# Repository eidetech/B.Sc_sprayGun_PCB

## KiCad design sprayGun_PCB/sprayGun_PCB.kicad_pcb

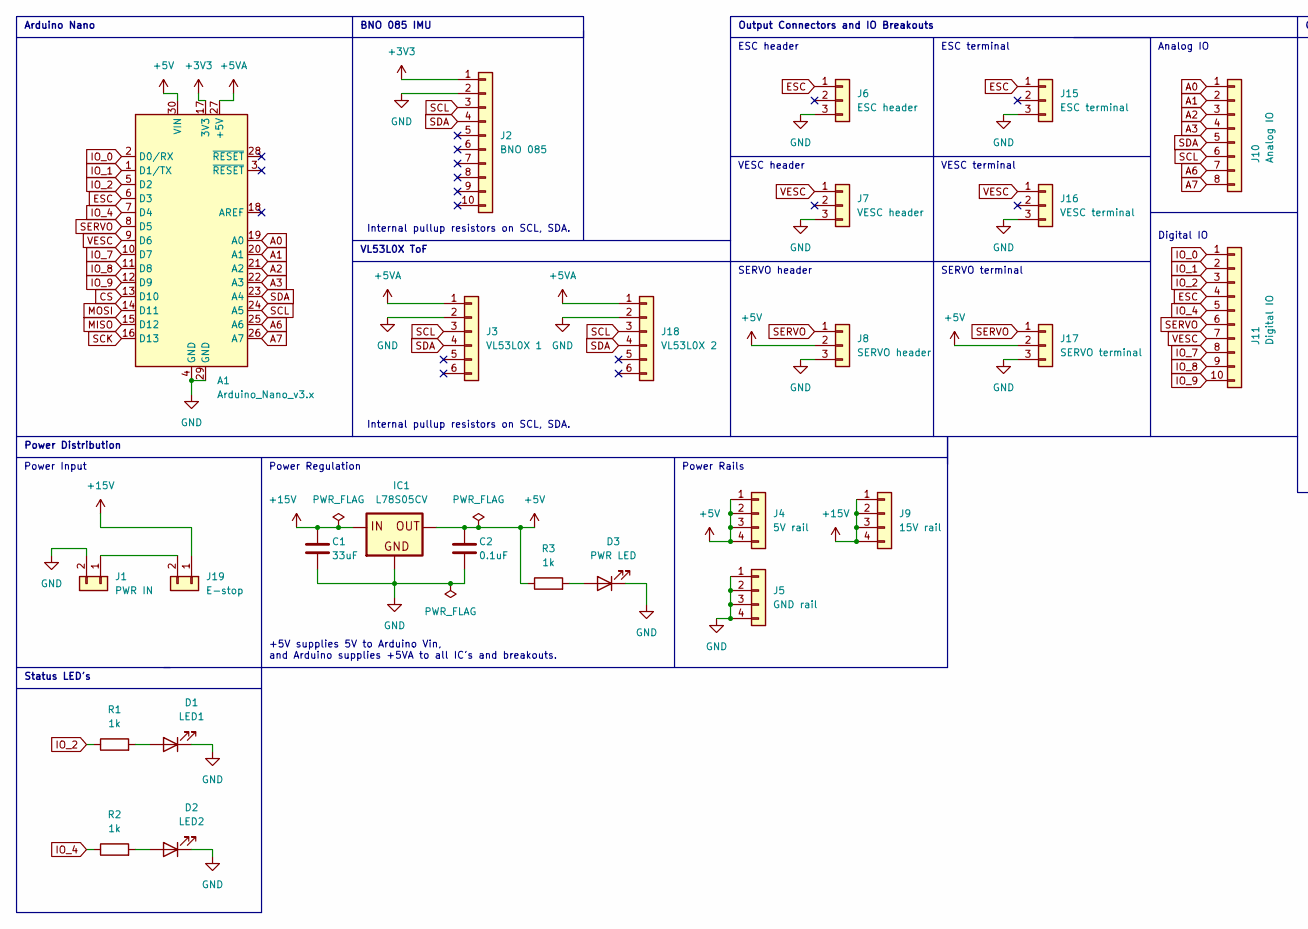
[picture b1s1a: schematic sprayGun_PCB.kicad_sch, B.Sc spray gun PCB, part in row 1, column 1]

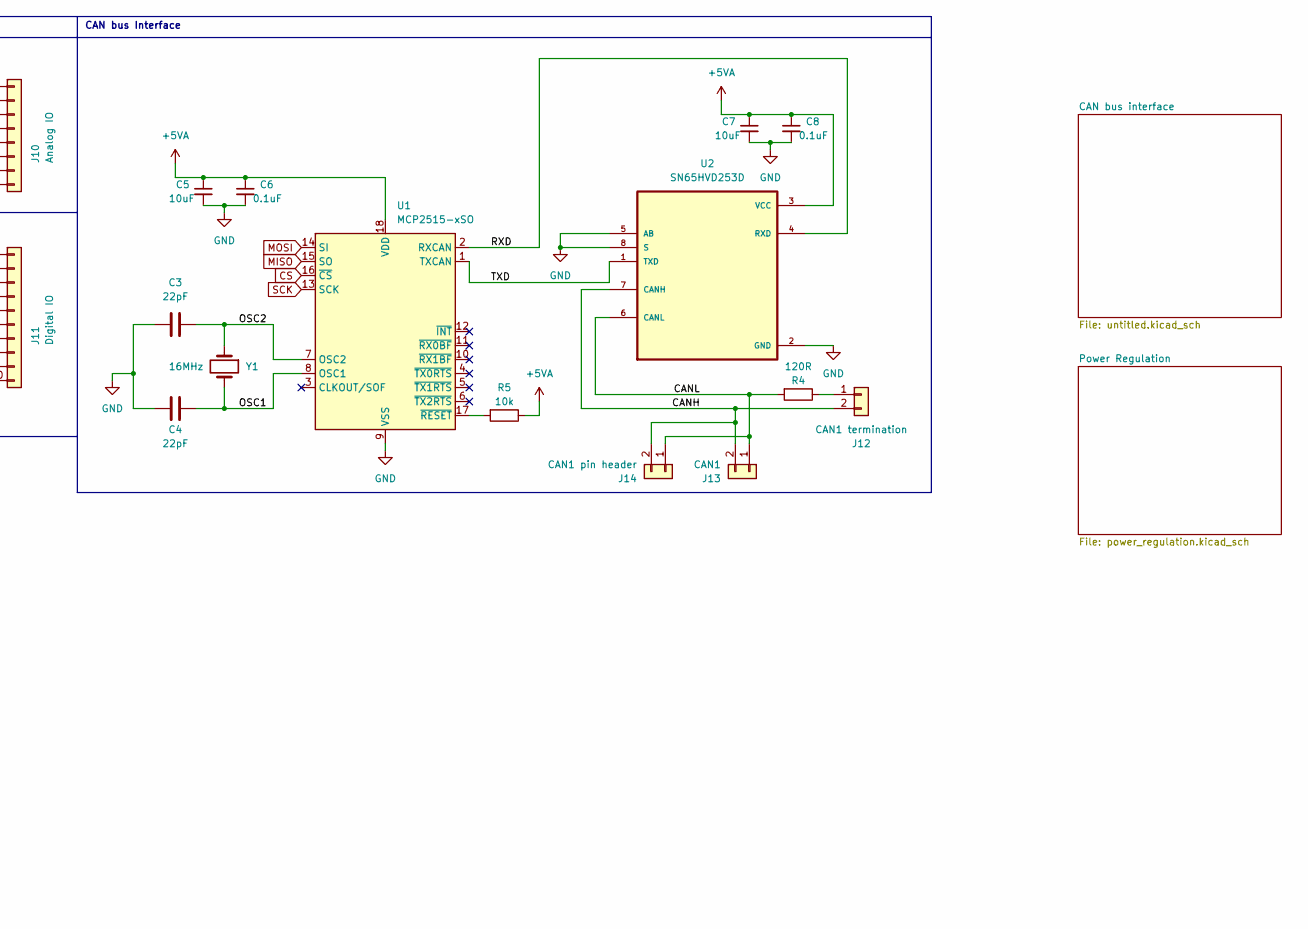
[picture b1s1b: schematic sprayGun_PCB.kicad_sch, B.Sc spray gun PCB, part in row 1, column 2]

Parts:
A1: Arduino_Nano_v3.x; Arduino_Nano
C1: 33uF; CP_Radial_D6.3mm_P2.50mm
C2, C6, C8: 0.1uF; CP_Radial_D5.0mm_P2.50mm
C3, C4: 22pF; CP_Radial_Tantal_D5.0mm_P2.50mm
C5, C7: 10uF; CP_Radial_D5.0mm_P2.00mm
D1: LED1; LED_D5.0mm
D2: LED2; LED_D5.0mm
D3: PWR LED; LED_D5.0mm
IC1: L78S05CV
J1: PWR IN; TerminalBlock_Phoenix_MKDS-3-2-5.08_1x02_P5.08mm_Horizontal
J2: BNO 085; PinSocket_1x10_P2.54mm_Vertical
J3: VL53L0X 1; JST_XH_B6B-XH-A_1x06_P2.50mm_Vertical
J4: 5V rail; TerminalBlock_Phoenix_MKDS-3-4-5.08_1x04_P5.08mm_Horizontal
J5: GND rail; TerminalBlock_Phoenix_MKDS-3-4-5.08_1x04_P5.08mm_Horizontal
J6: ESC header; PinHeader_1x03_P2.54mm_Vertical
J7: VESC header; PinHeader_1x03_P2.54mm_Vertical
J8: SERVO header; PinHeader_1x03_P2.54mm_Vertical
J9: 15V rail; TerminalBlock_Phoenix_MKDS-3-4-5.08_1x04_P5.08mm_Horizontal
J10: Analog IO; TerminalBlock_Phoenix_MKDS-3-8-5.08_1x08_P5.08mm_Horizontal
J11: Digital IO; TerminalBlock_Phoenix_MKDS-3-10-5.08_1x10_P5.08mm_Horizontal
J12: CAN1 termination; PinHeader_1x02_P2.54mm_Vertical
J13: CAN1; TerminalBlock_Phoenix_MKDS-3-2-5.08_1x02_P5.08mm_Horizontal
J14: CAN1 pin header; PinHeader_1x02_P2.54mm_Vertical
J15: ESC terminal; TerminalBlock_Phoenix_MKDS-3-3-5.08_1x03_P5.08mm_Horizontal
J16: VESC terminal; TerminalBlock_Phoenix_MKDS-3-3-5.08_1x03_P5.08mm_Horizontal
J17: SERVO terminal; TerminalBlock_Phoenix_MKDS-3-3-5.08_1x03_P5.08mm_Horizontal
J18: VL53L0X 2; JST_XH_B6B-XH-A_1x06_P2.50mm_Vertical
J19: E-stop; TerminalBlock_Phoenix_MKDS-3-2-5.08_1x02_P5.08mm_Horizontal
R1, R2, R3: 1k; R_Axial_DIN0207_L6.3mm_D2.5mm_P10.16mm_Horizontal
R4: 120R; R_Axial_DIN0207_L6.3mm_D2.5mm_P10.16mm_Horizontal
R5: 10k; R_Axial_DIN0207_L6.3mm_D2.5mm_P10.16mm_Horizontal
U1: MCP2515-xSO; SOIC-18W_7.5x11.6mm_P1.27mm
U2: SN65HVD253D
Y1: 16MHz; Crystal_HC49-4H_Vertical

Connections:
+3V3: A1.17 (3V3), J2.1
+5V: A1.30 (VIN), C2.1, IC1.3, J4.1, J4.2, J4.3, J4.4, J8.2, J17.2, R3.1
+5VA: A1.27 (+5V), C5.1, C6.1, C7.1, C8.1, J3.1, J18.1, R5.1, U1.18 (VDD), U2.3 (VCC)
+15V: C1.1, IC1.1, J9.1, J9.2, J9.3, J9.4, J19.1
/CANH: J12.2, J13.2, J14.2, U2.7 (CANH)
/CANL: J13.1, J14.1, R4.2, U2.6 (CANL)
/OSC1: C4.2, U1.8 (OSC1), Y1.2
/OSC2: C3.2, U1.7 (OSC2), Y1.1
/RXD: U1.2 (RXCAN), U2.4 (RXD)
/TXD: U1.1 (TXCAN), U2.1 (TXD)
A0: A1.19 (A0), J10.1
A1: A1.20 (A1), J10.2
A2: A1.21 (A2), J10.3
A3: A1.22 (A3), J10.4
A6: A1.25 (A6), J10.7
A7: A1.26 (A7), J10.8
CS: A1.13 (D10), U1.16 (~CS)
ESC: A1.6 (D3), J6.1, J11.4, J15.1
GND: A1.4 (GND), A1.29 (GND), C1.2, C2.2, C3.1, C4.1, C5.2, C6.2, C7.2, C8.2, D1.1 (K), D2.1 (K), D3.1 (K), IC1.2, J1.2, J2.2, J3.2, J5.1, J5.2, J5.3, J5.4, J6.3, J7.3, J8.3, J15.3, J16.3, J17.3, J18.2, U1.9 (VSS), U2.2 (GND), U2.5 (AB), U2.8 (S)
IO_0: A1.2 (D0/RX), J11.1
IO_1: A1.1 (D1/TX), J11.2
IO_2: A1.5 (D2), J11.3, R1.1
IO_4: A1.7 (D4), J11.5, R2.1
IO_7: A1.10 (D7), J11.8
IO_8: A1.11 (D8), J11.9
IO_9: A1.12 (D9), J11.10
MISO: A1.15 (D12), U1.15 (SO)
MOSI: A1.14 (D11), U1.14 (SI)
unnamed: D1.2 (A), R1.2
unnamed: D2.2 (A), R2.2
unnamed: D3.2 (A), R3.2
unnamed: J1.1, J19.2
unnamed: J12.1, R4.1
unnamed: R5.2, U1.17 (~RESET)
SCK: A1.16 (D13), U1.13 (SCK)
SCL: A1.24 (A5), J2.3, J3.3, J10.6, J18.3
SDA: A1.23 (A4), J2.4, J3.4, J10.5, J18.4
SERVO: A1.8 (D5), J8.1, J11.6, J17.1
VESC: A1.9 (D6), J7.1, J11.7, J16.1

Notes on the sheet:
Internal pullup resistors on SCL, SDA.
Power Rails
SERVO terminal
Digital IO
Analog IO
ESC terminal
+5V supplies 5V to Arduino Vin, and Arduino supplies +5VA to all IC's and breakouts.
VESC header
ESC header
Power Input
Output Connectors and IO Breakouts
BNO 085 IMU
Arduino Nano
CAN bus Interface
Power Regulation
Power Distribution
VL53L0X ToF
VESC terminal
SERVO header
Status LED's

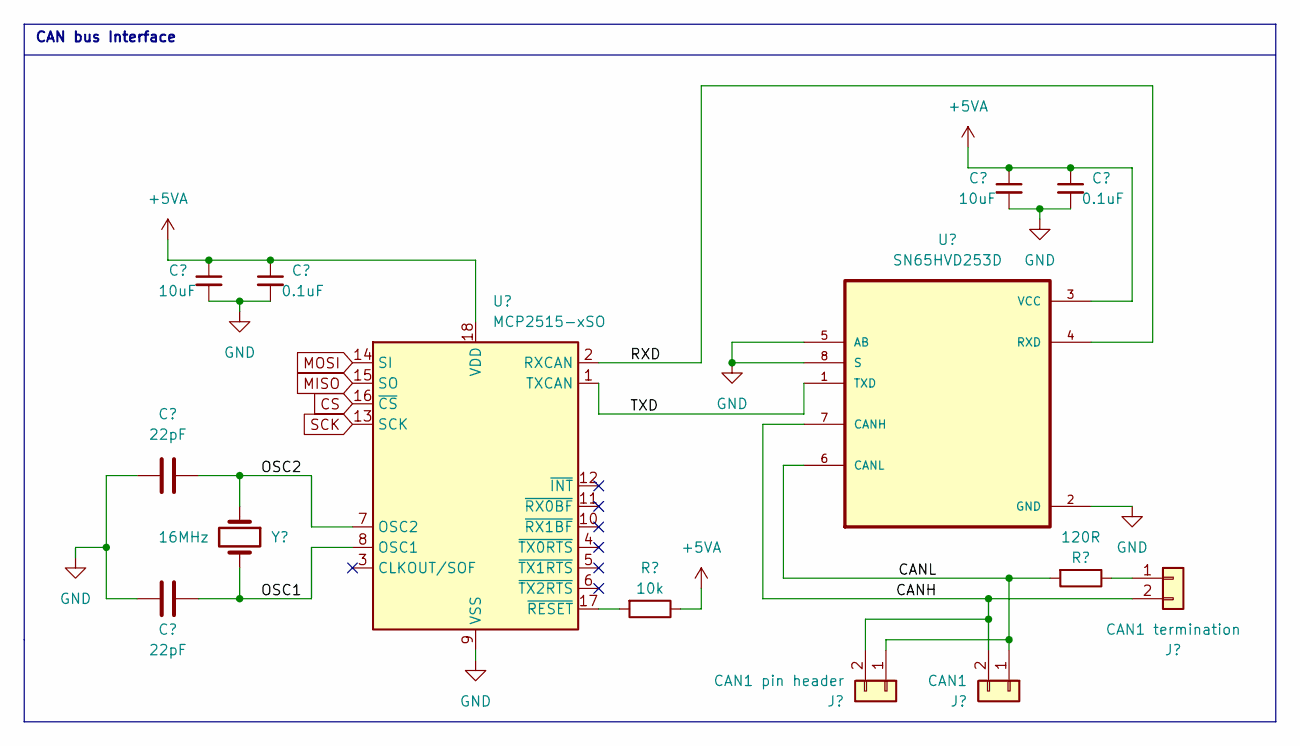
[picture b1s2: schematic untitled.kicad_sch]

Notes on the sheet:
CAN bus Interface

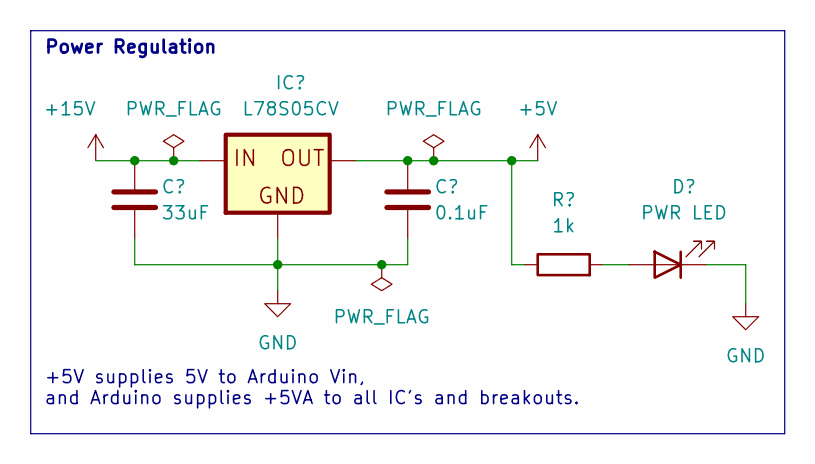
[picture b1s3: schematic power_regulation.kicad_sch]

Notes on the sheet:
Power Regulation
+5V supplies 5V to Arduino Vin, and Arduino supplies +5VA to all IC's and breakouts.

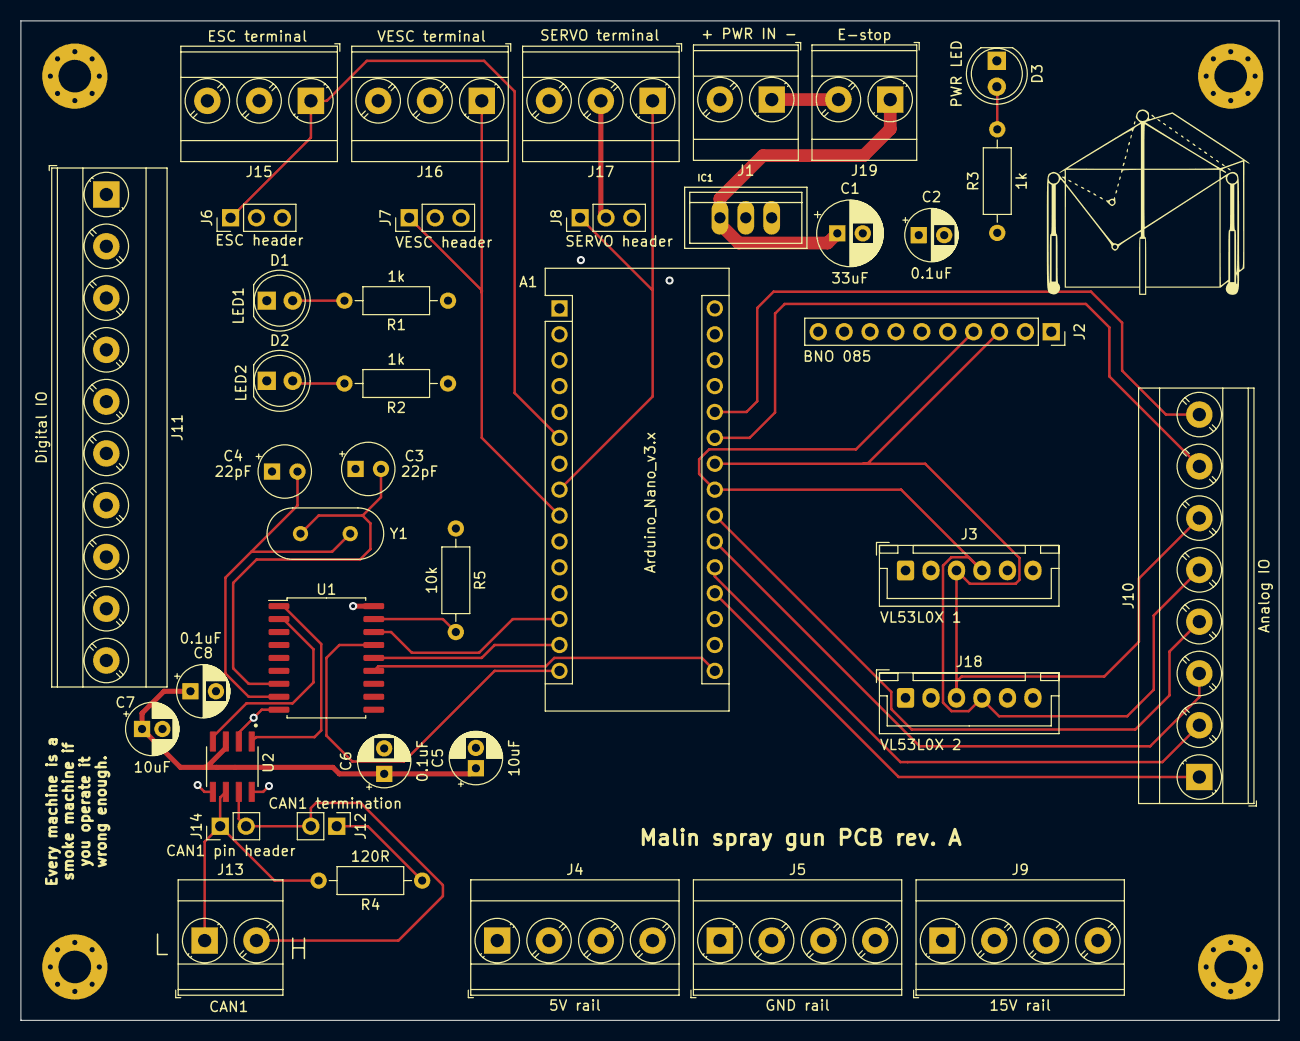
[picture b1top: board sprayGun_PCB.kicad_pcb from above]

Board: 4 copper layers, 123.4 x 98.1 mm, 40 parts (0 on the bottom side), 39 nets.

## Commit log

2022-04-11 Initial PCB schematics added.
2022-04-13 Rev A done
2022-04-13 This revision was sent to JLC for production.
2022-05-14 Exported step file o of PCB.
